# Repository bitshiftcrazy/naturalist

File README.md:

# The Naturalist

*A cyberdeck for the curious wanderer.*

The Naturalist is a tiny field computer built into a flea-market pencil case and designed to resemble the antique measuring instruments I collect. It features a Raspberry Pi Zero 2 W, a six-colour eInk display, a custom RP2040-based keyboard, and some aesthetically pleasing scavenged loot.

Its interior is inspired by old field guides and journals, and its first job is to accompany me into the woods as an offline mushroom field guide. The Naturalist is deliberately built around slowness and meant as an invitation to observe (and not just because the eInk takes up to 30 seconds to refresh!).

I enter a few mushroom characteristics using keyboard shortcuts, and my *Pilzapparat* (= mushroom apparatus) presents a handful of illustrated suggestions to browse and select for my virtual mushroom basket. It's a tool for exploration and not a food-safe mushroom guide (please do not base your decision which mushroom to lick on my database...).

And the illustrations aren't just random pictures. They're very much the point: I hand-selected them from the Biodiversity Heritage Library because I love the thought of a naturalist meticulously painting a mushroom 150 years ago, only for a weird woman to marvel at it on a 4-inch eInk display today. I'd love to add pages about the artists and naturalists in a future release, once I've sorted out the relevant rights and attribution details.

There's no cloud, no AI, or anything of the sort, simply because the process of hand-picking, marvelling, and observing is what makes this fun for me.

## Features

- Raspberry Pi Zero 2 W with a six-colour eInk display
- Custom RP2040-based, 42-key keyboard with a fancy ENIG finish
- Offline mushroom database and trait vocabulary
- Shortcut- and score-based search for illustrated mushroom candidates
- Virtual mushroom basket for collecting finds

## Repository Structure

    hardware/        KiCad PCB design, manufacturing files and artwork
      qmk/           QMK firmware for the Naturalist keyboard
    software/        Naturalist application software and assets
      data/          JSON data for mushrooms, traits and shortcuts
      assets/        Original and prepared mushroom illustrations
    pictures/        Naturalist glamour shots (and some less glamorous ones, too)

Detailed documentation lives in the relevant directories:

- [Hardware](hardware/README.md)
- [Keyboard firmware](hardware/qmk/keyboards/naturalist/README.md)
- [Software](software/README.md)

## Project Background

As usual with my personal projects, the Naturalist merges a few of my passions and preferences and, in doing so, "solves" problems that are probably uniquely mine. In this case: unusual computers, antique instruments, nature, and a somewhat odd lifelong obsession with mushrooms (I'm not exaggerating; I have proof ;)).

It started with a very simple idea back in March 2026, when I acquired a "new" antique ammeter for my collection and wondered how wonderful it would be to build a small computer into an antique measuring instrument. Luckily, not even I could bring myself to butcher an actual instrument. Then I found an antique wooden pencil case at a flea market, and the problem solved itself.

So what unique problem of mine does it actually solve? Well, it lets me collect things and turn them into little pieces of art without having to remove anything from the forest. And I get to indulge in some special-interest knowledge along the way.

For now, that means mushrooms. Eventually, I'd love to expand it to plants, minerals, maybe even birdsong (tho I'm really not a bird person ... yet ...).

One more thing about how I work on personal projects: I had the idea in March, designed the hardware in August and September, and took the Naturalist on its first mushroom walk in November. I often get questions on social media about when firmware or software will be available, but please remember that these are hobby projects. I'm always delighted when other people enjoy the same weirdness I do, but I work a full-time job, and this is a one-woman endeavour. If you're waiting for a release, think months, not days or weeks.

## Licenses

- **Hardware:** CERN-OHL-S v2
- **Data and illustrations:** The curated mushroom data is intended for release under CC0. Historical illustrations have their own provenance and rights information; please check the respective assets rather than assuming that one license covers everything.

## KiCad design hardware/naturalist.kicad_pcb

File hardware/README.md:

# The Naturalist Hardware

Hardware desgin and fabrication files for [The Naturalist Cyberdeck](../README.md), currently that's just the Naturalist keyboard. For my next PCB order, there's also a cover plate with integrated LiPo charger and USB ports planned, which will live here, too.

The Naturalist keyboard is a 42-key, RP2040-based board that uses small pushbuttons instead of switches, with a USB-C connector, it has a little silkscreen area for notes with a erasable marker.

## Hardware Overview

To build The Naturalist exactly as shown in the pics, you'll need:

- a wooden case with internal dimensions of at least 16 × 10 cm and a depth of at least 1.6 cm
- a Raspberry Pi Zero 2 W
- a Pimoroni Inky Impression 4-inch Spectra 6 display
- an Adafruit Power Boost 1000C
- a LiPo battery (ideally at least 2000 mAh)
- a warm white LED noodle
- two toggle switches (one for power, one for the light)
- the Naturalist keyboard (see design files here and its BOM)
- the 3D printed parts (see `STL/`)
- brass picture hangers and a leather strap if you want to wear it as a purse
- some (faux) leather for decoration
- a small piece of corkboard

Keep in mind that mine lives in a flea-market pencil case and the 3D-printed parts and mounting positions may need some adjustments to fit yours.

## Directory Structure

The KiCad keyboard design files are in this directory. The other files are organized as follows:

    fabrication/    Gerber files, a ready and tested Gerber ZIP, and PCB assembly files
    qmk/            QMK keyboard firmware files
    STL/           3D-printable covers and mounting parts
    libraries/      Project-specific KiCad symbols and footprints

## Manufacturing of the keyboard

The `fabrication/` directory contains a zipped set of Gerbers that was manufactured and tested. 
You can upload this ZIP to a PCB manufacturer, or regenerate the Gerbers from the KiCad project.

The same directory also includes a BOM and placement files for JLCPCB assembly if you want the board populated for you (not an ad, I just like to order there because I'm impatient, and they're the fastest for my location in my experience).

### Keyboard BOM

Just a quick overview, see `fabrication/` for manufacturing BOMs

<table>
  <thead>
    <tr><th align="right">Qty</th><th>Component</th><th>Description</th></tr>
  </thead>
  <tbody>
    <tr><td align="right">1</td><td>RP2040</td><td>Microcontroller</td></tr>
    <tr><td align="right">1</td><td>W25Q128JVSIQ</td><td>128 Mbit QSPI Flash</td></tr>
    <tr><td align="right">1</td><td>ABM8-272-T3</td><td>12 MHz crystal</td></tr>
    <tr><td align="right">1</td><td>AP2112K-3.3TRG1</td><td>3.3 V voltage regulator</td></tr>
    <tr><td align="right">1</td><td>USB4105-GF-A</td><td>USB-C connector</td></tr>
    <tr><td align="right">1</td><td>USBLC6-2P6</td><td>USB ESD protection</td></tr>
    <tr><td align="right">42</td><td>1N4148WS</td><td>Switching diodes, SOD-323</td></tr>
    <tr><td align="right">42</td><td>TS-1188U-C</td><td>Keyboard switches</td></tr>
    <tr><td align="right">2</td><td>KMR221G-LFS</td><td>BOOTSEL and RESET buttons</td></tr>
    <tr><td align="right">11</td><td>100 nF</td><td>Capacitors, 0603</td></tr>
    <tr><td align="right">4</td><td>1 µF</td><td>Capacitors, 0603</td></tr>
    <tr><td align="right">2</td><td>15 pF</td><td>Capacitors, 0603</td></tr>
    <tr><td align="right">2</td><td>1 kΩ</td><td>Resistors, 0603</td></tr>
    <tr><td align="right">2</td><td>5.1 kΩ</td><td>Resistors, 0603</td></tr>
    <tr><td align="right">1</td><td>10 kΩ</td><td>Resistor, 0603</td></tr>
    <tr><td align="right">1</td><td>0 Ω</td><td>Resistor, 0603</td></tr>
    <tr><td align="right">2</td><td>27 Ω</td><td>Resistors, 0603</td></tr>
  </tbody>
</table>

### Keyboard Firmware

See [QMK README](./qmk/keyboards/naturalist/README.md)

## License

The keyboard hardware design is licensed under the **CERN Open Hardware Licence Version 2 – Strongly Reciprocal (CERN-OHL-S v2)**.

You may manufacture, modify, and sell products based on this design, subject to the conditions of the license, including its requirements for sharing modified design sources when applicable.

The full license text is in the `LICENSE` file. Other components, software, and third-party parts have their own licensing terms.

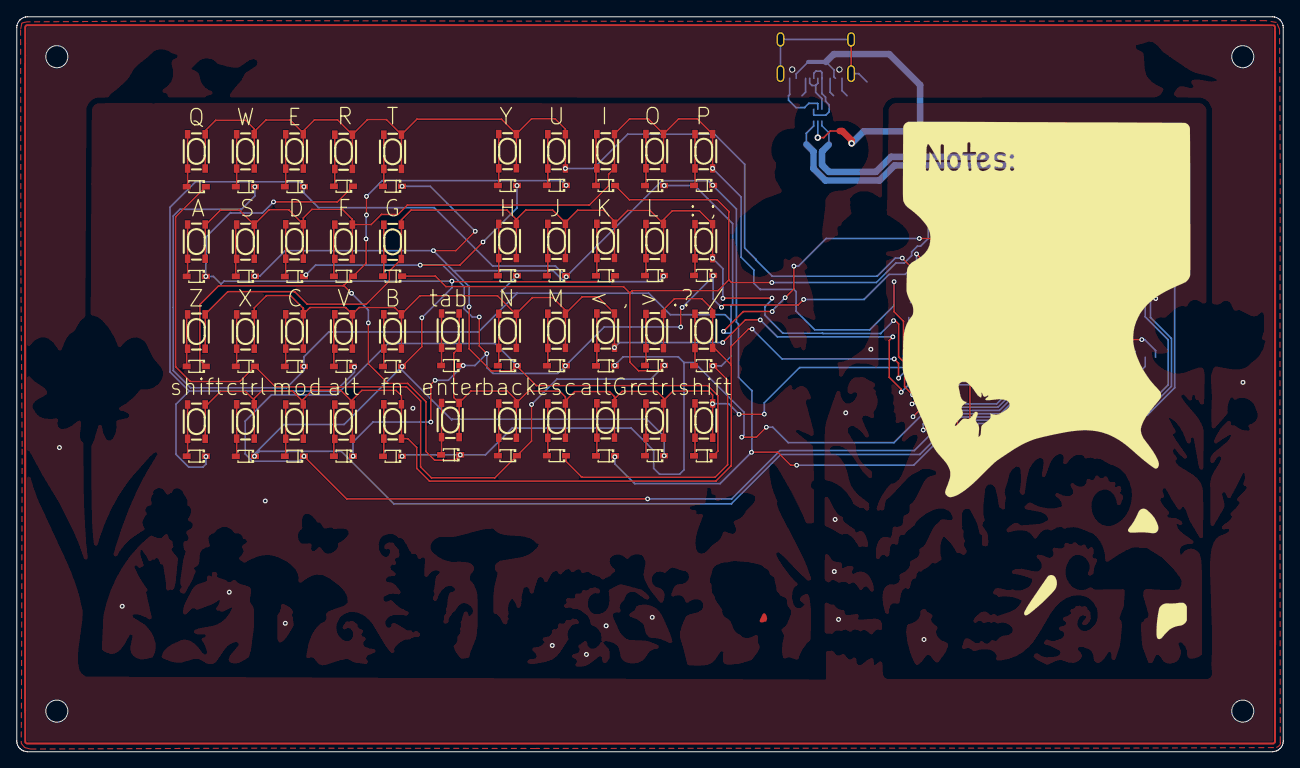
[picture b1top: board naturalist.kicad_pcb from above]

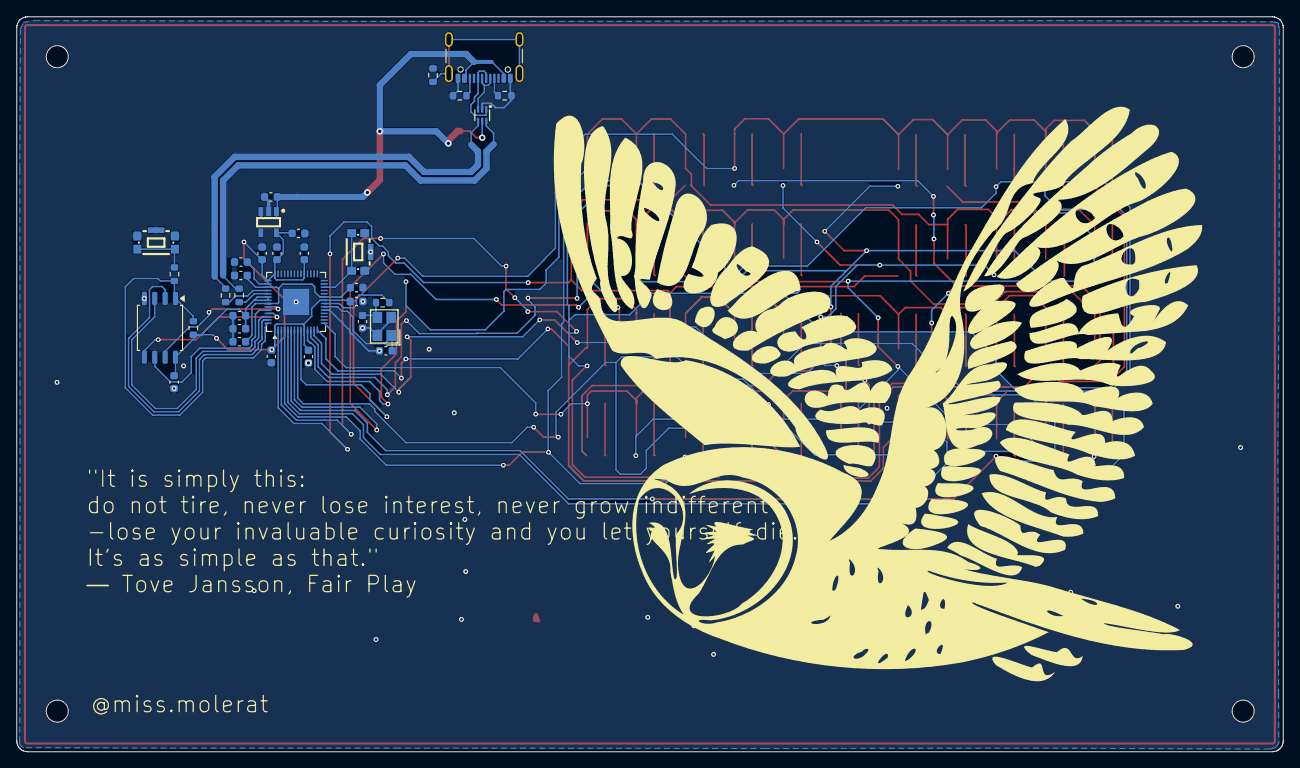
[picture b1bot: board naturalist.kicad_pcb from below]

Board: 2 copper layers, 154.9 x 89.9 mm, 117 parts (33 on the bottom side), 79 nets.

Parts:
C_ADCAVDD1: 100nF; C_0603_1608Metric
C_DVDD1, C_DVDD2: 100nF; C_0603_1608Metric
C_FLASH1: 100nF; C_0603_1608Metric
C_IOVDD1, C_IOVDD2, C_IOVDD3, C_IOVDD4, C_IOVDD5, C_IOVDD6: 100nF; C_0603_1608Metric
C_LDO_IN1: 1uF; C_0603_1608Metric
C_LDO_OUT1: 1uF; C_0603_1608Metric
C_USBVDD1: 100nF; C_0603_1608Metric
C_VREGIN1: 1uF; C_0603_1608Metric
C_VREGOUT1: 1uF; C_0603_1608Metric
C_XIN1: 15pF; C_0603_1608Metric
C_XOUT1: 15pF; C_0603_1608Metric
D1: SOT-666-6_L1.6-W1.2-P0.50-LS1.6-BR
D2, D3, D4, D5, D6, D7, D8, D9, D10, D11, D12, D13, D14, D15, D16, D17, D18, D19, D20, D21, D22, D23, D24, D25, D26, D27, D28, D29, D30, D31, D32, D33, D34, D35, D36, D37, D38, D39, D40, D41, D42, D43: D; SOD-323_L1.8-W1.3-LS2.5-RD
J1: USB_C_Receptacle_USB2.0_16P; USB_C_Receptacle_GCT_USB4105-xx-A_16P_TopMnt_Horizontal
R_BOOT1: 1kOhm; R_0603_1608Metric
R_CC1, R_CC2: 5.1kOhm; R_0603_1608Metric
R_CS_PULL1: 10kOm; R_0603_1608Metric
R_SHIELD1: 0Ohm; R_0603_1608Metric
R_USB_DM1: 27Ohm; R_0603_1608Metric
R_USB_DP1: 27Ohm; R_0603_1608Metric
R_XOUT1: 1kOhm; R_0603_1608Metric
SW1, SW2, SW3, SW4, SW5, SW6, SW7, SW8, SW9, SW10, SW11, SW12, SW13, SW14, SW15, SW16, SW17, SW18, SW19, SW20, SW21, SW22, SW23, SW24, SW25, SW26, SW27, SW28, SW29, SW30, SW31, SW32, SW33, SW34, SW35, SW36, SW37, SW38, SW39, SW40, SW41, SW42: KEY-SMD_4P-L4.2-W3.2-P2.20-LS4.6
SW_BOOTSEL1: KEY-SMD_KMR2XXGXXX
SW_RST1: KEY-SMD_KMR2XXGXXX
U1: W25Q128JVS; SOIC-8_5.3x5.3mm_P1.27mm
U2: SOT-25-5_L2.9-W1.6-P0.95-LS2.8-BL
U3: RP2040; QFN-56-1EP_7x7mm_P0.4mm_EP3.2x3.2mm
Y1: 12MHz; CRYSTAL-SMD_4P-L3.2-W2.5-BL

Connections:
/COL0: D2.1 (K), D9.1 (K), D16.1 (K), D23.1 (K), D30.1 (K), D37.1 (K), U3.2 (GPIO0)
/COL1: D3.1 (K), D10.1 (K), D17.1 (K), D24.1 (K), D31.1 (K), D38.1 (K), U3.3 (GPIO1)
/COL2: D4.1 (K), D11.1 (K), D18.1 (K), D25.1 (K), D32.1 (K), D39.1 (K), U3.4 (GPIO2)
/COL3: D5.1 (K), D12.1 (K), D19.1 (K), D26.1 (K), D33.1 (K), D40.1 (K), U3.5 (GPIO3)
/COL4: D6.1 (K), D13.1 (K), D20.1 (K), D27.1 (K), D34.1 (K), D41.1 (K), U3.6 (GPIO4)
/COL5: D7.1 (K), D14.1 (K), D21.1 (K), D28.1 (K), D35.1 (K), D42.1 (K), U3.7 (GPIO5)
/COL6: D8.1 (K), D15.1 (K), D22.1 (K), D29.1 (K), D36.1 (K), D43.1 (K), U3.8 (GPIO6)
/ROW0: SW1.1, SW1.2, SW2.1, SW2.2, SW3.1, SW3.2, SW4.1, SW4.2, SW5.1, SW5.2, SW6.1, SW6.2, SW7.1, SW7.2, U3.9 (GPIO7)
/ROW1: SW8.1, SW8.2, SW9.1, SW9.2, SW10.1, SW10.2, SW11.1, SW11.2, SW12.1, SW12.2, SW13.1, SW13.2, SW14.1, SW14.2, U3.11 (GPIO8)
/ROW2: SW15.1, SW15.2, SW16.1, SW16.2, SW17.1, SW17.2, SW18.1, SW18.2, SW19.1, SW19.2, SW20.1, SW20.2, SW21.1, SW21.2, U3.12 (GPIO9)
/ROW3: SW22.1, SW22.2, SW23.1, SW23.2, SW24.1, SW24.2, SW25.1, SW25.2, SW26.1, SW26.2, SW27.1, SW27.2, SW28.1, SW28.2, U3.13 (GPIO10)
/ROW4: SW29.1, SW29.2, SW30.1, SW30.2, SW31.1, SW31.2, SW32.1, SW32.2, SW33.1, SW33.2, SW34.1, SW34.2, SW35.1, SW35.2, U3.14 (GPIO11)
/ROW5: SW36.1, SW36.2, SW37.1, SW37.2, SW38.1, SW38.2, SW39.1, SW39.2, SW40.1, SW40.2, SW41.1, SW41.2, SW42.1, SW42.2, U3.15 (GPIO12)
/RP2040_CORE/1V1: C_DVDD1.1, C_DVDD2.1, C_VREGOUT1.1, U3.23 (DVDD), U3.45 (VREG_VOUT), U3.50 (DVDD)
/RP2040_CORE/3V3: C_ADCAVDD1.1, C_FLASH1.2, C_IOVDD1.1, C_IOVDD2.1, C_IOVDD3.1, C_IOVDD4.1, C_IOVDD5.1, C_IOVDD6.1, C_LDO_OUT1.1, C_USBVDD1.1, C_VREGIN1.1, R_CS_PULL1.1, U1.8 (VCC), U2.5 (VOUT), U3.1 (IOVDD), U3.10 (IOVDD), U3.22 (IOVDD), U3.33 (IOVDD), U3.42 (IOVDD), U3.43 (ADC_AVDD), U3.44 (VREG_VIN), U3.48 (USB_VDD), U3.49 (IOVDD)
/RP2040_CORE/CC1: J1.A5 (CC1), R_CC1.1
/RP2040_CORE/CC2: J1.B5 (CC2), R_CC2.1
/RP2040_CORE/GND: C_ADCAVDD1.2, C_DVDD1.2, C_DVDD2.2, C_FLASH1.1, C_IOVDD1.2, C_IOVDD2.2, C_IOVDD3.2, C_IOVDD4.2, C_IOVDD5.2, C_IOVDD6.2, C_LDO_IN1.2, C_LDO_OUT1.2, C_USBVDD1.2, C_VREGIN1.2, C_VREGOUT1.2, C_XIN1.1, C_XOUT1.1, D1.2 (GND), J1.A1 (GND), J1.A12 (GND), J1.B1 (GND), J1.B12 (GND), R_CC1.2, R_CC2.2, R_SHIELD1.2, SW_BOOTSEL1.1, SW_BOOTSEL1.2, SW_BOOTSEL1.5, SW_RST1.1, SW_RST1.2, SW_RST1.5, U1.4 (GND), U2.2 (GND), U3.19 (TESTEN), U3.57 (GND), Y1.2 (G), Y1.4 (G)
/RP2040_CORE/QSPI_SCLK: U1.6 (CLK), U3.52 (QSPI_SCLK)
/RP2040_CORE/QSPI_SD0: U1.5 (DI/IO_{0}), U3.53 (QSPI_SD0)
/RP2040_CORE/QSPI_SD1: U1.2 (DO/IO_{1}), U3.55 (QSPI_SD1)
/RP2040_CORE/QSPI_SD2: U1.3 (~WP/IO_{2}), U3.54 (QSPI_SD2)
/RP2040_CORE/QSPI_SD3: U1.7 (~HOLD/~RESET/IO_{3}), U3.51 (QSPI_SD3)
/RP2040_CORE/QSPI_SS: R_BOOT1.1, R_CS_PULL1.2, U1.1 (~CS), U3.56 (~QSPI_SS)
/RP2040_CORE/RUN: SW_RST1.3, SW_RST1.4, U3.26 (RUN)
/RP2040_CORE/USB_BOOT: R_BOOT1.2, SW_BOOTSEL1.3, SW_BOOTSEL1.4
/RP2040_CORE/USB_CONN+: D1.6 (I/O1), R_USB_DP1.2
/RP2040_CORE/USB_CONN-: D1.4 (I/O2), R_USB_DM1.2
/RP2040_CORE/USB_DM: R_USB_DM1.1, U3.46 (USB_DM)
/RP2040_CORE/USB_DM_RAW: D1.3 (I/O2), J1.A7 (D-), J1.B7 (D-)
/RP2040_CORE/USB_DP: R_USB_DP1.1, U3.47 (USB_DP)
/RP2040_CORE/USB_DP_RAW: D1.1 (I/O1), J1.A6 (D+), J1.B6 (D+)
/RP2040_CORE/USB_SHIELD: J1.SH (SHIELD), R_SHIELD1.1
/RP2040_CORE/VBUS: C_LDO_IN1.1, D1.5 (VBUS), J1.A4 (VBUS), J1.A9 (VBUS), J1.B4 (VBUS), J1.B9 (VBUS), U2.1 (VIN), U2.3 (EN)
/RP2040_CORE/XIN: C_XIN1.2, U3.20 (XIN), Y1.1
/RP2040_CORE/XOUT: R_XOUT1.2, U3.21 (XOUT)
unnamed: C_XOUT1.2, R_XOUT1.1, Y1.3
unnamed: D2.2 (A), SW1.3, SW1.4
unnamed: D3.2 (A), SW2.3, SW2.4
unnamed: D4.2 (A), SW3.3, SW3.4
unnamed: D5.2 (A), SW4.3, SW4.4
unnamed: D6.2 (A), SW5.3, SW5.4
unnamed: D7.2 (A), SW6.3, SW6.4
unnamed: D8.2 (A), SW7.3, SW7.4
unnamed: D9.2 (A), SW8.3, SW8.4
unnamed: D10.2 (A), SW9.3, SW9.4
unnamed: D11.2 (A), SW10.3, SW10.4
unnamed: D12.2 (A), SW11.3, SW11.4
unnamed: D13.2 (A), SW12.3, SW12.4
unnamed: D14.2 (A), SW13.3, SW13.4
unnamed: D15.2 (A), SW14.3, SW14.4
unnamed: D16.2 (A), SW15.3, SW15.4
unnamed: D17.2 (A), SW16.3, SW16.4
unnamed: D18.2 (A), SW17.3, SW17.4
unnamed: D19.2 (A), SW18.3, SW18.4
unnamed: D20.2 (A), SW19.3, SW19.4
unnamed: D21.2 (A), SW20.3, SW20.4
unnamed: D22.2 (A), SW21.3, SW21.4
unnamed: D23.2 (A), SW22.3, SW22.4
unnamed: D24.2 (A), SW23.3, SW23.4
unnamed: D25.2 (A), SW24.3, SW24.4
unnamed: D26.2 (A), SW25.3, SW25.4
unnamed: D27.2 (A), SW26.3, SW26.4
unnamed: D28.2 (A), SW27.3, SW27.4
unnamed: D29.2 (A), SW28.3, SW28.4
unnamed: D30.2 (A), SW29.3, SW29.4
unnamed: D31.2 (A), SW30.3, SW30.4
unnamed: D32.2 (A), SW31.3, SW31.4
unnamed: D33.2 (A), SW32.3, SW32.4
unnamed: D34.2 (A), SW33.3, SW33.4
unnamed: D35.2 (A), SW34.3, SW34.4
unnamed: D36.2 (A), SW35.3, SW35.4
unnamed: D37.2 (A), SW36.3, SW36.4
unnamed: D38.2 (A), SW37.3, SW37.4
unnamed: D39.2 (A), SW38.3, SW38.4
unnamed: D40.2 (A), SW39.3, SW39.4
unnamed: D41.2 (A), SW40.3, SW40.4
unnamed: D42.2 (A), SW41.3, SW41.4
unnamed: D43.2 (A), SW42.3, SW42.4

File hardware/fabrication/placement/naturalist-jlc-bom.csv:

Comment,Designator,Footprint,JLCPCB Part # optional
100nF,"C_ADCAVDD1,C_DVDD1,C_DVDD2,C_FLASH1,C_IOVDD1,C_IOVDD2,C_IOVDD3,C_IOVDD4,C_IOVDD5,C_IOVDD6,C_USBVDD1",Capacitor_SMD:C_0603_1608Metric,
1uF,"C_LDO_IN1,C_LDO_OUT1,C_VREGIN1,C_VREGOUT1",Capacitor_SMD:C_0603_1608Metric,
15pF,"C_XIN1,C_XOUT1",Capacitor_SMD:C_0603_1608Metric,
,D1,naturalist:SOT-666-6_L1.6-W1.2-P0.50-LS1.6-BR,C15999
D,"D2,D3,D4,D5,D6,D7,D8,D9,D10,D11,D12,D13,D14,D15,D16,D17,D18,D19,D20,D21,D22,D23,D24,D25,D26,D27,D28,D29,D30,D31,D32,D33,D34,D35,D36,D37,D38,D39,D40,D41,D42,D43",naturalist:SOD-323_L1.8-W1.3-LS2.5-RD,C181133
USB_C_Receptacle_USB2.0_16P,J1,Connector_USB:USB_C_Receptacle_GCT_USB4105-xx-A_16P_TopMnt_Horizontal,C3020560
1kOhm,"R_BOOT1,R_XOUT1",Resistor_SMD:R_0603_1608Metric,
5.1kOhm,"R_CC1,R_CC2",Resistor_SMD:R_0603_1608Metric,
10kOm,R_CS_PULL1,Resistor_SMD:R_0603_1608Metric,
0Ohm,R_SHIELD1,Resistor_SMD:R_0603_1608Metric,
27Ohm,"R_USB_DM1,R_USB_DP1",Resistor_SMD:R_0603_1608Metric,
,"SW1,SW2,SW3,SW4,SW5,SW6,SW7,SW8,SW9,SW10,SW11,SW12,SW13,SW14,SW15,SW16,SW17,SW18,SW19,SW20,SW21,SW22,SW23,SW24,SW25,SW26,SW27,SW28,SW29,SW30,SW31,SW32,SW33,SW34,SW35,SW36,SW37,SW38,SW39,SW40,SW41,SW42",naturalist:KEY-SMD_4P-L4.2-W3.2-P2.20-LS4.6,C2939245
,"SW_BOOTSEL1,SW_RST1",naturalist:KEY-SMD_KMR2XXGXXX,C72443
W25Q128JVS,U1,Package_SO:SOIC-8_5.3x5.3mm_P1.27mm,C97521
,U2,naturalist:SOT-25-5_L2.9-W1.6-P0.95-LS2.8-BL,C51118
RP2040,U3,Package_DFN_QFN:QFN-56-1EP_7x7mm_P0.4mm_EP3.2x3.2mm,C2040
12MHz,Y1,naturalist:CRYSTAL-SMD_4P-L3.2-W2.5-BL,C20625731
